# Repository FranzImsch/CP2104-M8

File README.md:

# CP2104-M8

CP2104 Breakout Board with USB-C and Reset Circuit for ESP-Chips. Features standard FTDI-Header as well as Tag Connect (TC2030) header (Check schematic for pinout). Components were selected so that only Basic Parts from JLCPCB's SMT Assembly Service are used (With the exception of the voltage regulator!).

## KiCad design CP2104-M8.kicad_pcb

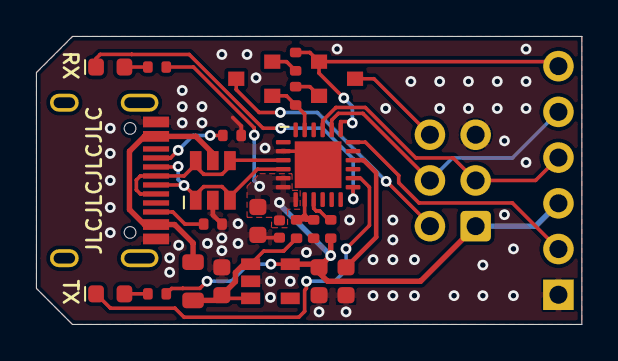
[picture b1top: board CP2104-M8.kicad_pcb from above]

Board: 2 copper layers, 30.3 x 16.0 mm, 25 parts (0 on the bottom side), 24 nets.

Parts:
C1: 100nF; C_0402_1005Metric
C2, C4, C5: 2.2µF; C_0603_1608Metric
C3: 4.7µF; C_0603_1608Metric
D1: TX-LED; LED_0603_1608Metric
D2: RX-LED; LED_0603_1608Metric
FB1: Ferrite_Bead_Small; L_0805_2012Metric
J1: C393939 Conn; USB_C_Receptacle_HRO_TYPE-C-31-M-12
J2: Tag-Connect-Out; IDC-Header_2x03_P2.54mm_Vertical
Je: FTDI-EQUIV; PinSocket_1x06_P2.54mm_Horizontal
Q2: S8050; SOT-23
Qe: S8050; SOT-23
R1, R2: 1kΩ; R_0402_1005Metric
R3: 5.1kΩ; R_0402_1005Metric
R4: 24kΩ; R_0402_1005Metric
R5: 47kΩ; R_0402_1005Metric
R6: 5.1Ω; R_0402_1005Metric
R7: 4.7kΩ; R_0402_1005Metric
R8, R9: 10kΩ; R_0402_1005Metric
U1: CP2104; QFN-24-1EP_4x4mm_P0.5mm_EP2.6x2.6mm
U2: TLV75533PDBV; SOT-23-5
U3: SRV05-4; SOT-23-6

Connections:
+3V3: C1.1, C2.1, C5.1, J2.1, Je.3, R1.2, R2.2, R7.1, U1.5, U1.6, U1.7, U2.5
CTS: Je.2, U1.18
D+: J1.A6, J1.B6, U1.3, U3.4, U3.6
D-: J1.A7, J1.B7, U1.4, U3.1, U3.3
DTR: Q2.1, R8.1, U1.23
GND: C1.2, C2.2, C3.1, C4.1, C5.2, J1.A1, J1.A12, J1.B1, J1.B12, J2.5, Je.1, R3.1, R5.1, R6.2, U1.2, U1.25, U2.2, U3.2
GPIO0: J2.2, Q2.3
unnamed: C3.2, U1.16
unnamed: D1.1, U1.14
unnamed: D1.2, R1.1
unnamed: D2.1, U1.13
unnamed: D2.2, R2.1
unnamed: J1.A5, R6.1
unnamed: J1.B5, R3.2
unnamed: Qe.2, R8.2
unnamed: Q2.2, R9.2
unnamed: R4.1, R5.2, U1.8
unnamed: R7.2, U1.9
RESET: J2.6, Qe.3
RTS: Je.6, Qe.1, R9.1, U1.19
RXD: J2.4, Je.5, U1.20
TXD: J2.3, Je.4, U1.21
VBUS: C4.2, FB1.1, R4.2, U2.1, U2.3
VDD: FB1.2, J1.A4, J1.A9, J1.B4, J1.B9, U3.5

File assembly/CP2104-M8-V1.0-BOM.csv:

Comment,Designator,Footprint,LCSC
"100nF","C1","Capacitor_SMD:C_0402_1005Metric","C1525"
"4.7µF","C3","Capacitor_SMD:C_0603_1608Metric","C19666"
"2.2µF","C2,C4,C5","Capacitor_SMD:C_0603_1608Metric","C23630"
"TX-LED","D1","LED_SMD:LED_0603_1608Metric","C72043"
"RX-LED","D2","LED_SMD:LED_0603_1608Metric","C72041"
"Ferrite_Bead_Small","FB1","Inductor_SMD:L_0805_2012Metric","C1015"
"C393939 Conn","J1","Connector_USB:USB_C_Receptacle_HRO_TYPE-C-31-M-12",""
"Tag-Connect-Out","J2","Connector_IDC:IDC-Header_2x03_P2.54mm_Vertical",""
"FTDI-EQUIV","J3","Connector_PinSocket_2.54mm:PinSocket_1x06_P2.54mm_Horizontal",""
"S8050","Q1,Q2","Package_TO_SOT_SMD:SOT-23","C2146"
"1kΩ","R1,R2","Resistor_SMD:R_0402_1005Metric","C11702"
"5.1kΩ","R3,R6","Resistor_SMD:R_0402_1005Metric","C25905"
"24kΩ","R4","Resistor_SMD:R_0402_1005Metric","C25769"
"47kΩ","R5","Resistor_SMD:R_0402_1005Metric","C25792"
"4.7kΩ","R7","Resistor_SMD:R_0402_1005Metric","C25900"
"10kΩ","R8,R9","Resistor_SMD:R_0402_1005Metric","C25744"
"CP2104","U1","Package_DFN_QFN:QFN-24-1EP_4x4mm_P0.5mm_EP2.6x2.6mm","C47742"
"TLV75533PDBV","U2","Package_TO_SOT_SMD:SOT-23-5",""
"SRV05-4","U3","Package_TO_SOT_SMD:SOT-23-6","C85364"

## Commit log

2020-12-31 initialise repo
2020-12-31 added schematic
